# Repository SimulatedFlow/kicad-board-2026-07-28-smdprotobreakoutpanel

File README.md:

# 2026-07-28-smdprotobreakoutpanel

<!-- SF-STORE-BLOCK:BEGIN -->
## 🛒 Source-available — see before you buy

This repository contains the **full design files** of a commercial hardware board. It is **source-available, not open source**: read it, evaluate it, then buy a license to use it. See **LICENSE.md (source-available, purchase required)**.

**Get it / Buy:**
- eBay store — all our boards and PCB art: https://www.ebay.de/usr/simula-9
- Merch shop (dev & gaming): https://simulatedflow.myspreadshop.de
- Merch shop (Synthetica / EDM): https://synthetica.myspreadshop.de
- Direct / invoice (Simulated Flow UG): simulatedflow@gmail.com

_This board has no eBay item number of its own listed here — the store link above holds all current listings._

### 📬 **Free Board Documentation & Firmware Pack**

Schematics, BOMs and example-firmware docs for our STM32 carrier boards. Get it by joining the newsletter — plus a heads-up when something new ships. Double opt-in, unsubscribe in one click, no address sharing.

👉 **[Get the free pack](https://simulatedflow.teufel-engineering.com/newsletter/hardware/?q=gh)**

_© 2026 Simulated Flow UG. All rights reserved._
<!-- SF-STORE-BLOCK:END -->

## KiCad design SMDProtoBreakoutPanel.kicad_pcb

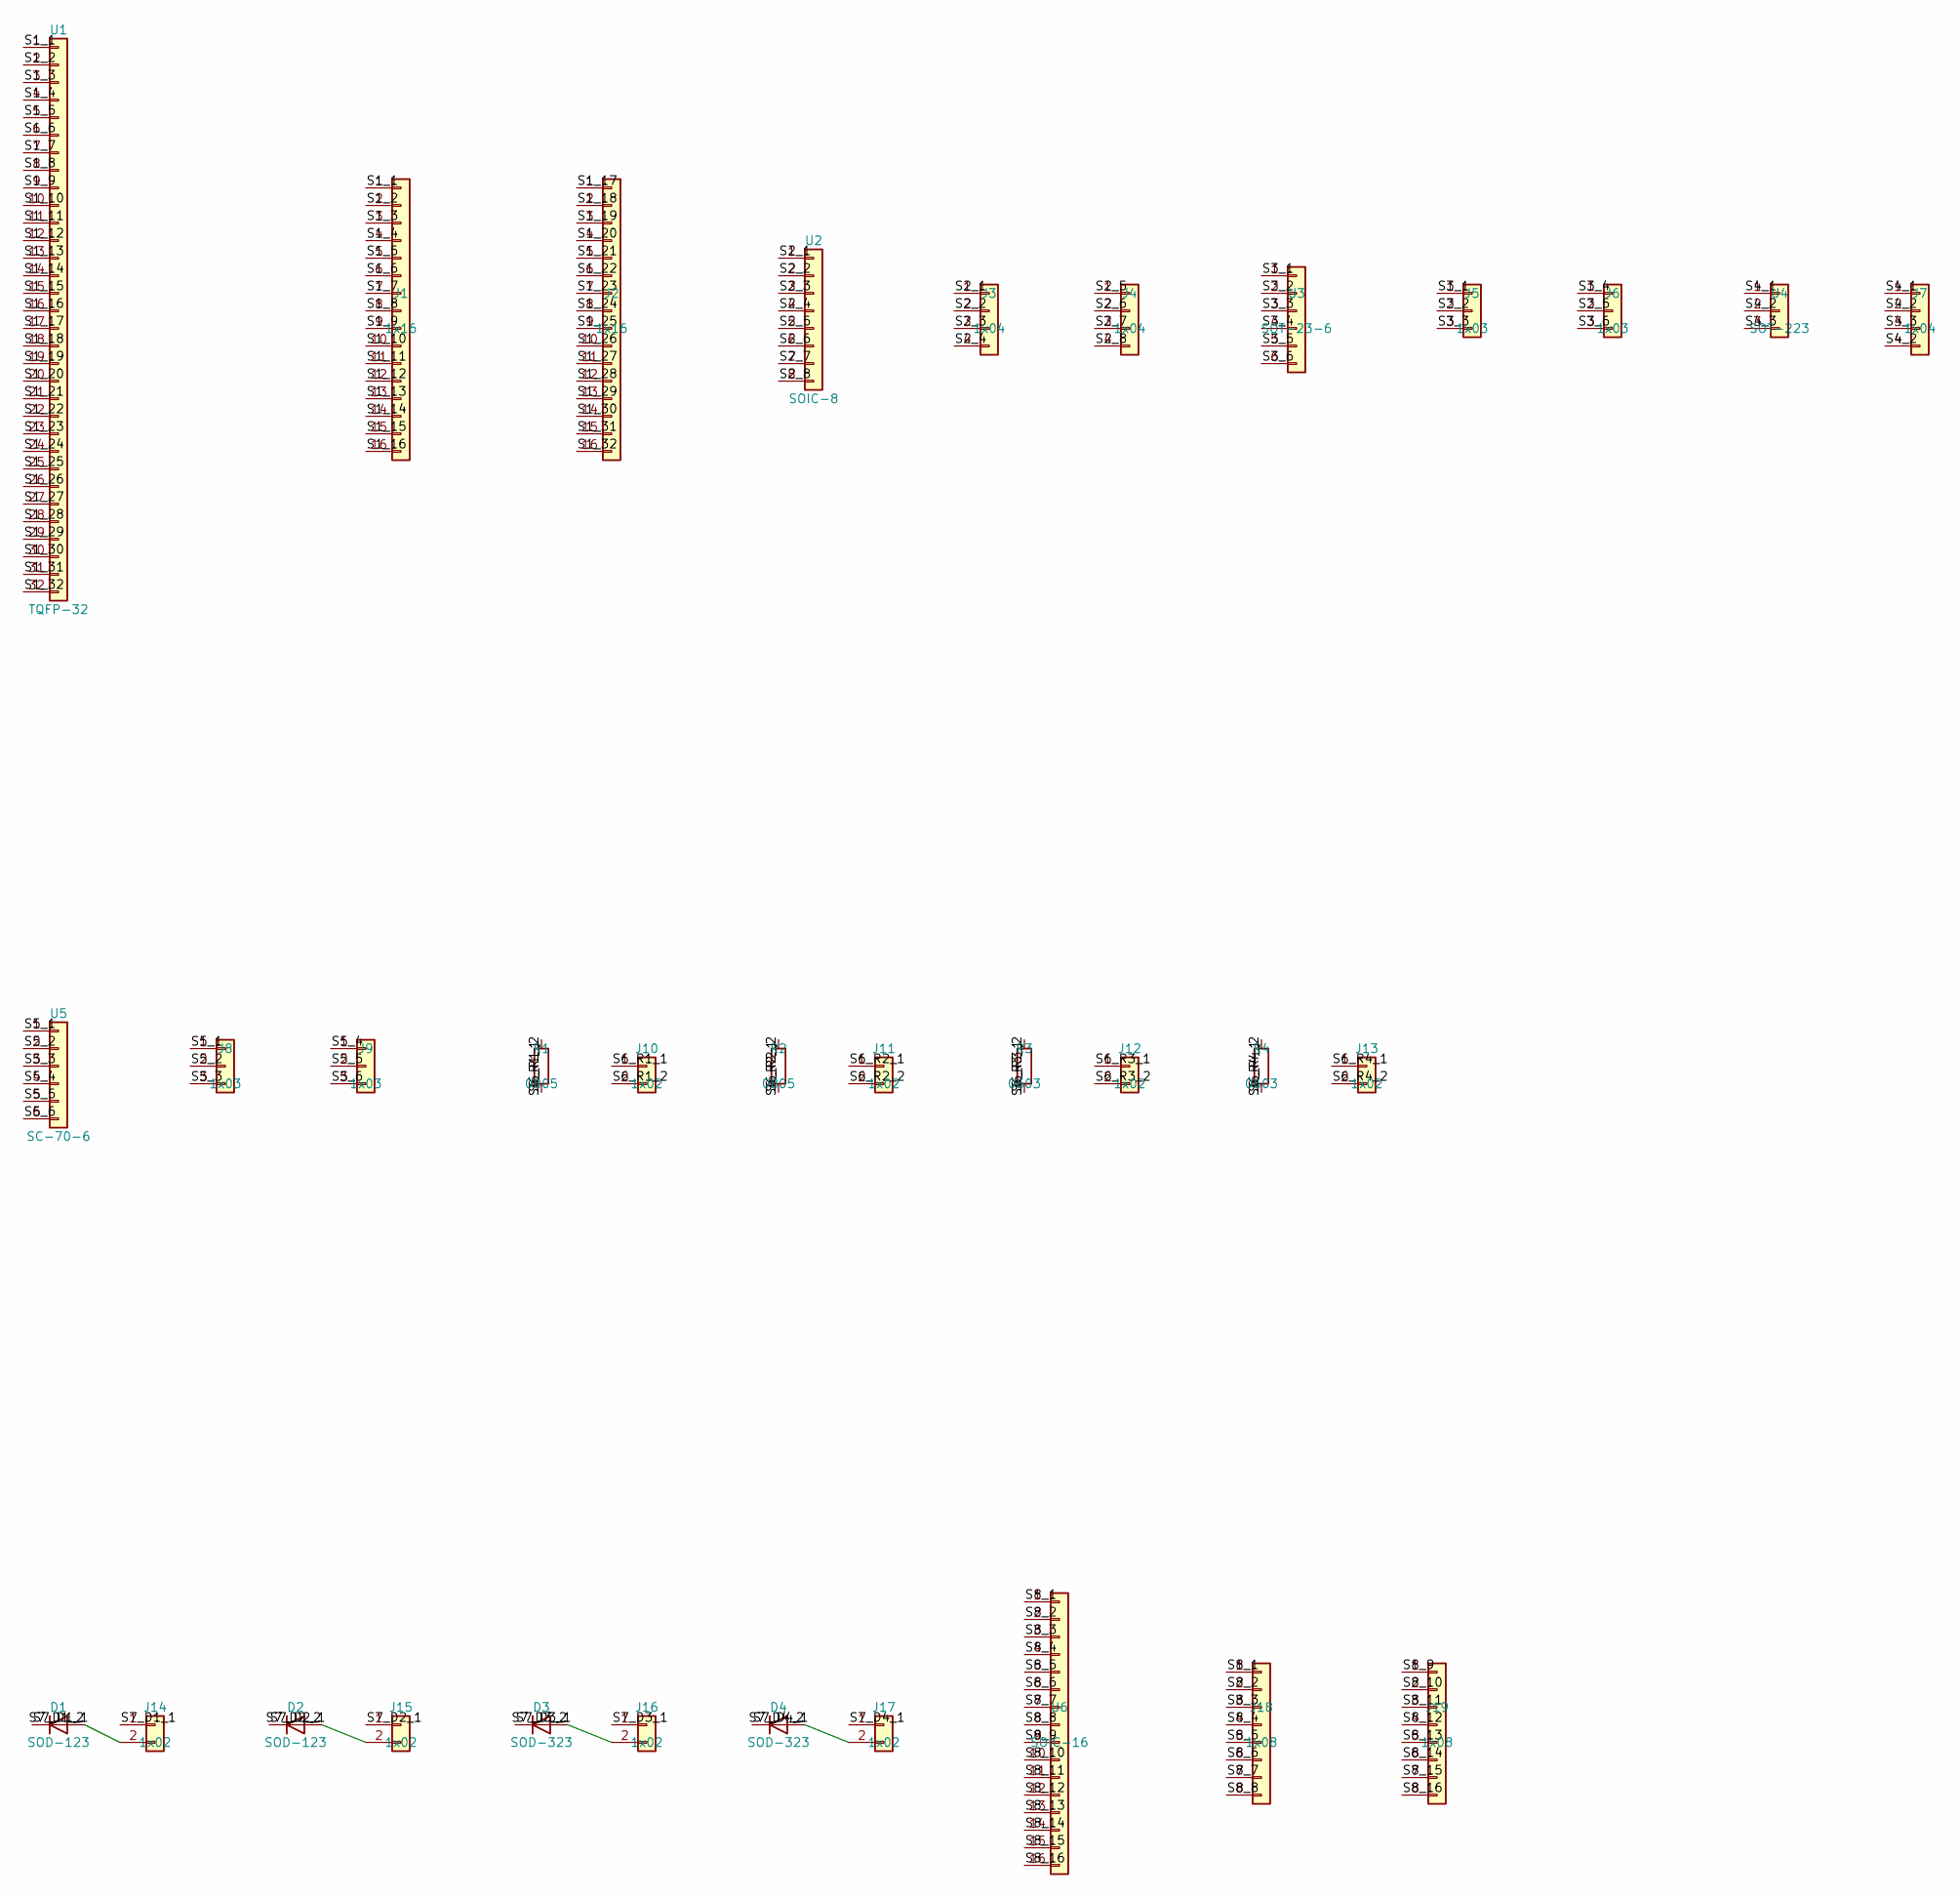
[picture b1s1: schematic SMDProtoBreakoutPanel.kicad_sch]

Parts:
D1, D2: SOD-123; D_SOD-123
D3, D4: SOD-323; D_SOD-323_HandSoldering
J1, J2: 1x16; PinHeader_1x16_P2.54mm_Vertical
J3, J4, J7: 1x04; PinHeader_1x04_P2.54mm_Vertical
J5, J6, J8, J9: 1x03; PinHeader_1x03_P2.54mm_Vertical
J10, J11, J12, J13, J14, J15, J16, J17: 1x02; PinHeader_1x02_P2.54mm_Vertical
J18, J19: 1x08; PinHeader_1x08_P2.54mm_Vertical
R1, R2: 0805; R_0805_2012Metric_Pad1.20x1.40mm_HandSolder
R3, R4: 0603; R_0603_1608Metric_Pad0.98x0.95mm_HandSolder
U1: TQFP-32; TQFP-32_7x7mm_P0.8mm
U2: SOIC-8; SOIC-8_3.9x4.9mm_P1.27mm
U3: SOT-23-6; SOT-23-6_Handsoldering
U4: SOT-223; SOT-223-3_TabPin2
U5: SC-70-6; SOT-363_SC-70-6
U6: SOIC-16; SOIC-16_3.9x9.9mm_P1.27mm

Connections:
S1_1: J1.1, U1.1
S1_2: J1.2, U1.2
S1_3: J1.3, U1.3
S1_4: J1.4, U1.4
S1_5: J1.5, U1.5
S1_6: J1.6, U1.6
S1_7: J1.7, U1.7
S1_8: J1.8, U1.8
S1_9: J1.9, U1.9
S1_10: J1.10, U1.10
S1_11: J1.11, U1.11
S1_12: J1.12, U1.12
S1_13: J1.13, U1.13
S1_14: J1.14, U1.14
S1_15: J1.15, U1.15
S1_16: J1.16, U1.16
S1_17: J2.1, U1.17
S1_18: J2.2, U1.18
S1_19: J2.3, U1.19
S1_20: J2.4, U1.20
S1_21: J2.5, U1.21
S1_22: J2.6, U1.22
S1_23: J2.7, U1.23
S1_24: J2.8, U1.24
S1_25: J2.9, U1.25
S1_26: J2.10, U1.26
S1_27: J2.11, U1.27
S1_28: J2.12, U1.28
S1_29: J2.13, U1.29
S1_30: J2.14, U1.30
S1_31: J2.15, U1.31
S1_32: J2.16, U1.32
S2_1: J3.1, U2.1
S2_2: J3.2, U2.2
S2_3: J3.3, U2.3
S2_4: J3.4, U2.4
S2_5: J4.1, U2.5
S2_6: J4.2, U2.6
S2_7: J4.3, U2.7
S2_8: J4.4, U2.8
S3_1: J5.1, U3.1
S3_2: J5.2, U3.2
S3_3: J5.3, U3.3
S3_4: J6.1, U3.4
S3_5: J6.2, U3.5
S3_6: J6.3, U3.6
S4_1: J7.1, U4.1
S4_2: J7.2, J7.4, U4.2
S4_3: J7.3, U4.3
S5_1: J8.1, U5.1
S5_2: J8.2, U5.2
S5_3: J8.3, U5.3
S5_4: J9.1, U5.4
S5_5: J9.2, U5.5
S5_6: J9.3, U5.6
S6_R1_1: J10.1, R1.1
S6_R1_2: J10.2, R1.2
S6_R2_1: J11.1, R2.1
S6_R2_2: J11.2, R2.2
S6_R3_1: J12.1, R3.1
S6_R3_2: J12.2, R3.2
S6_R4_1: J13.1, R4.1
S6_R4_2: J13.2, R4.2
S7_D1_1: D1.1 (K), J14.1
S7_D1_2: D1.2 (A), J14.2
S7_D2_1: D2.1 (K), J15.1
S7_D2_2: D2.2 (A), J15.2
S7_D3_1: D3.1 (K), J16.1
S7_D3_2: D3.2 (A), J16.2
S7_D4_1: D4.1 (K), J17.1
S7_D4_2: D4.2 (A), J17.2
S8_1: J18.1, U6.1
S8_2: J18.2, U6.2
S8_3: J18.3, U6.3
S8_4: J18.4, U6.4
S8_5: J18.5, U6.5
S8_6: J18.6, U6.6
S8_7: J18.7, U6.7
S8_8: J18.8, U6.8
S8_9: J19.1, U6.9
S8_10: J19.2, U6.10
S8_11: J19.3, U6.11
S8_12: J19.4, U6.12
S8_13: J19.5, U6.13
S8_14: J19.6, U6.14
S8_15: J19.7, U6.15
S8_16: J19.8, U6.16

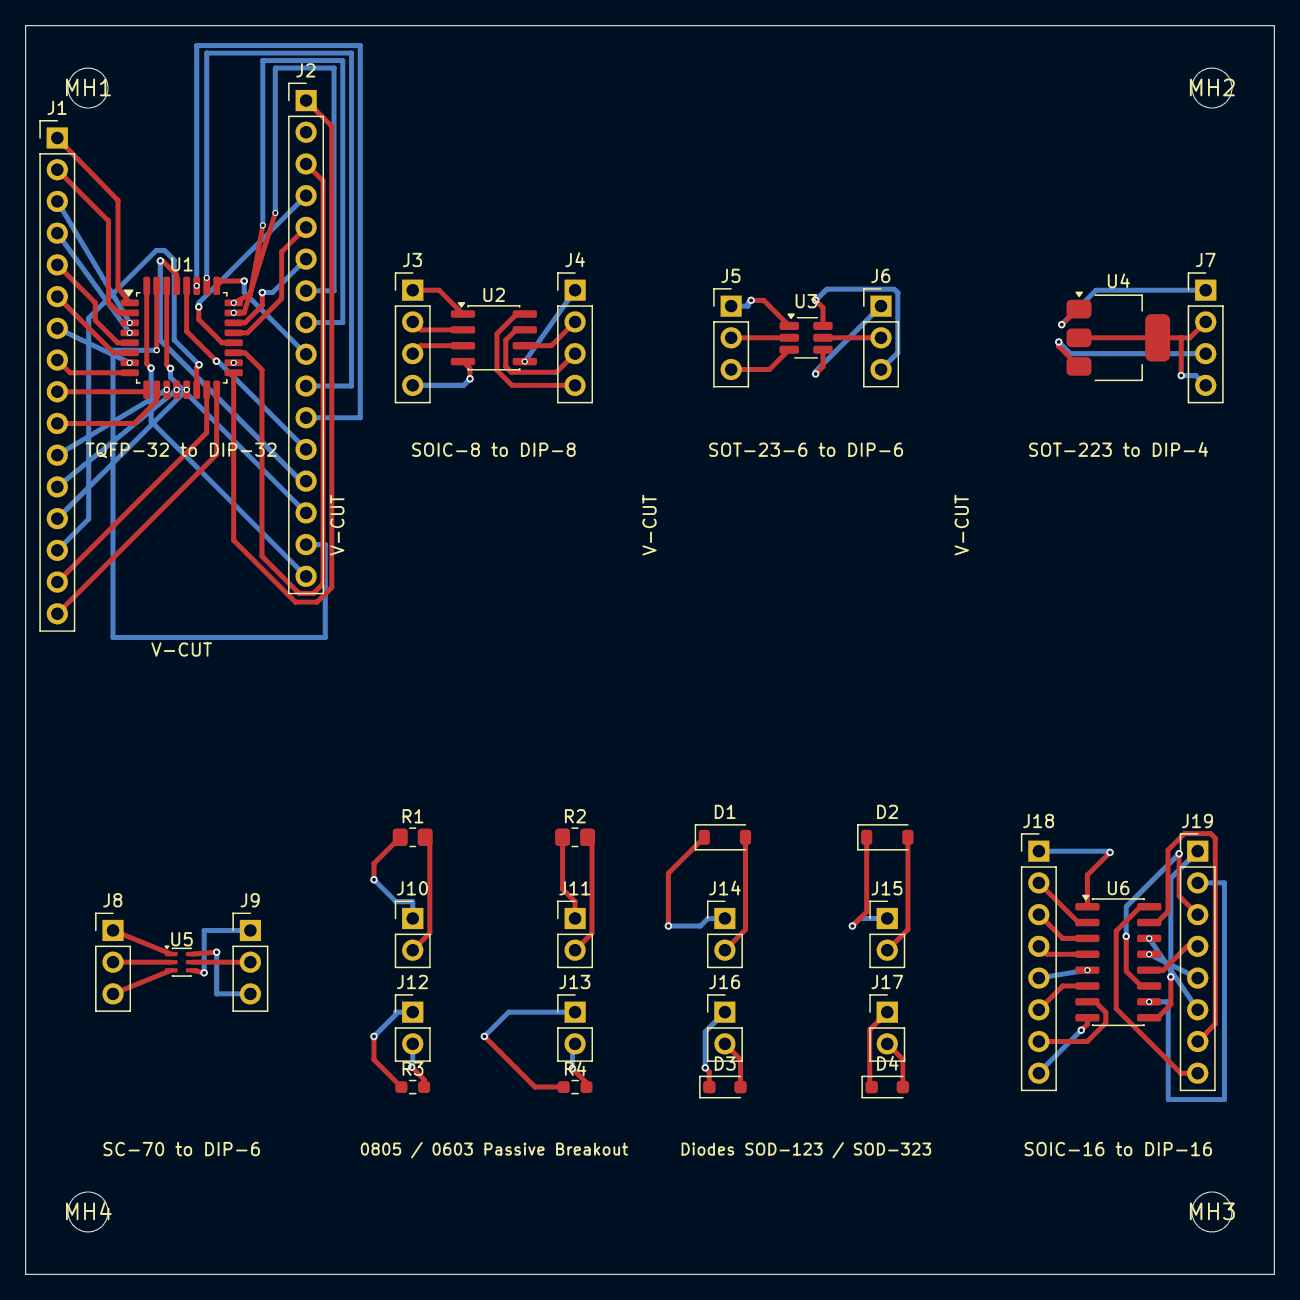
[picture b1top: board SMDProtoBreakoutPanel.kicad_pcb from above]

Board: 4 copper layers, 100.0 x 100.0 mm, 37 parts (0 on the bottom side), 87 nets.

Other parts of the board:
MH1, MH2, MH3, MH4: MountingHole_3.2mm
